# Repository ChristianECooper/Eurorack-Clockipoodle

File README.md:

### Clockipoodle
Clockipoodle is a clock module designed for use in a Eurorack modular synthesizer.

It's based on an Arduino nano, driving a Darlington Array, the UI is:
- a 128x64 pixel SSD1306 display,
- a switched rotary encoder,
- 2 x momentary buttons
- 6 x 3.5mm standard jacks

As of version 1.1 it supports the following options:
1. Direct setting of BPM via a rotary encoder.
2. Indirect setting of the BPM, using the rotary encoder to set, then pressing the encoder to apply.
3. Four additional outputs labelled A through to D that can be a multuplied, divided, duplicate or a disabled copy of the main clock.
4. Tap to set BPM.
5. Adjustable pulse width.
6. Play/Pause.
7. Reset the various outputs to be in sync again.

There is also an unused input currenly labeled as 'CV IN' and and associated LED, which may become a Clock in or CV input that drives a parameter (or parameters) to be later defined.
The current design is limited to 0-5V so could only really increase the tempo, so the next iteration is likely to support -5 to +5v so that decreasing tempo from a CV input is an option.
In the meantime I'm considering using the CV input to adjust a swing component of the beat.

All input and output jacks are protected against over voltage and negative voltages for safety.

This is my first stab at a module design, comments are welcome.

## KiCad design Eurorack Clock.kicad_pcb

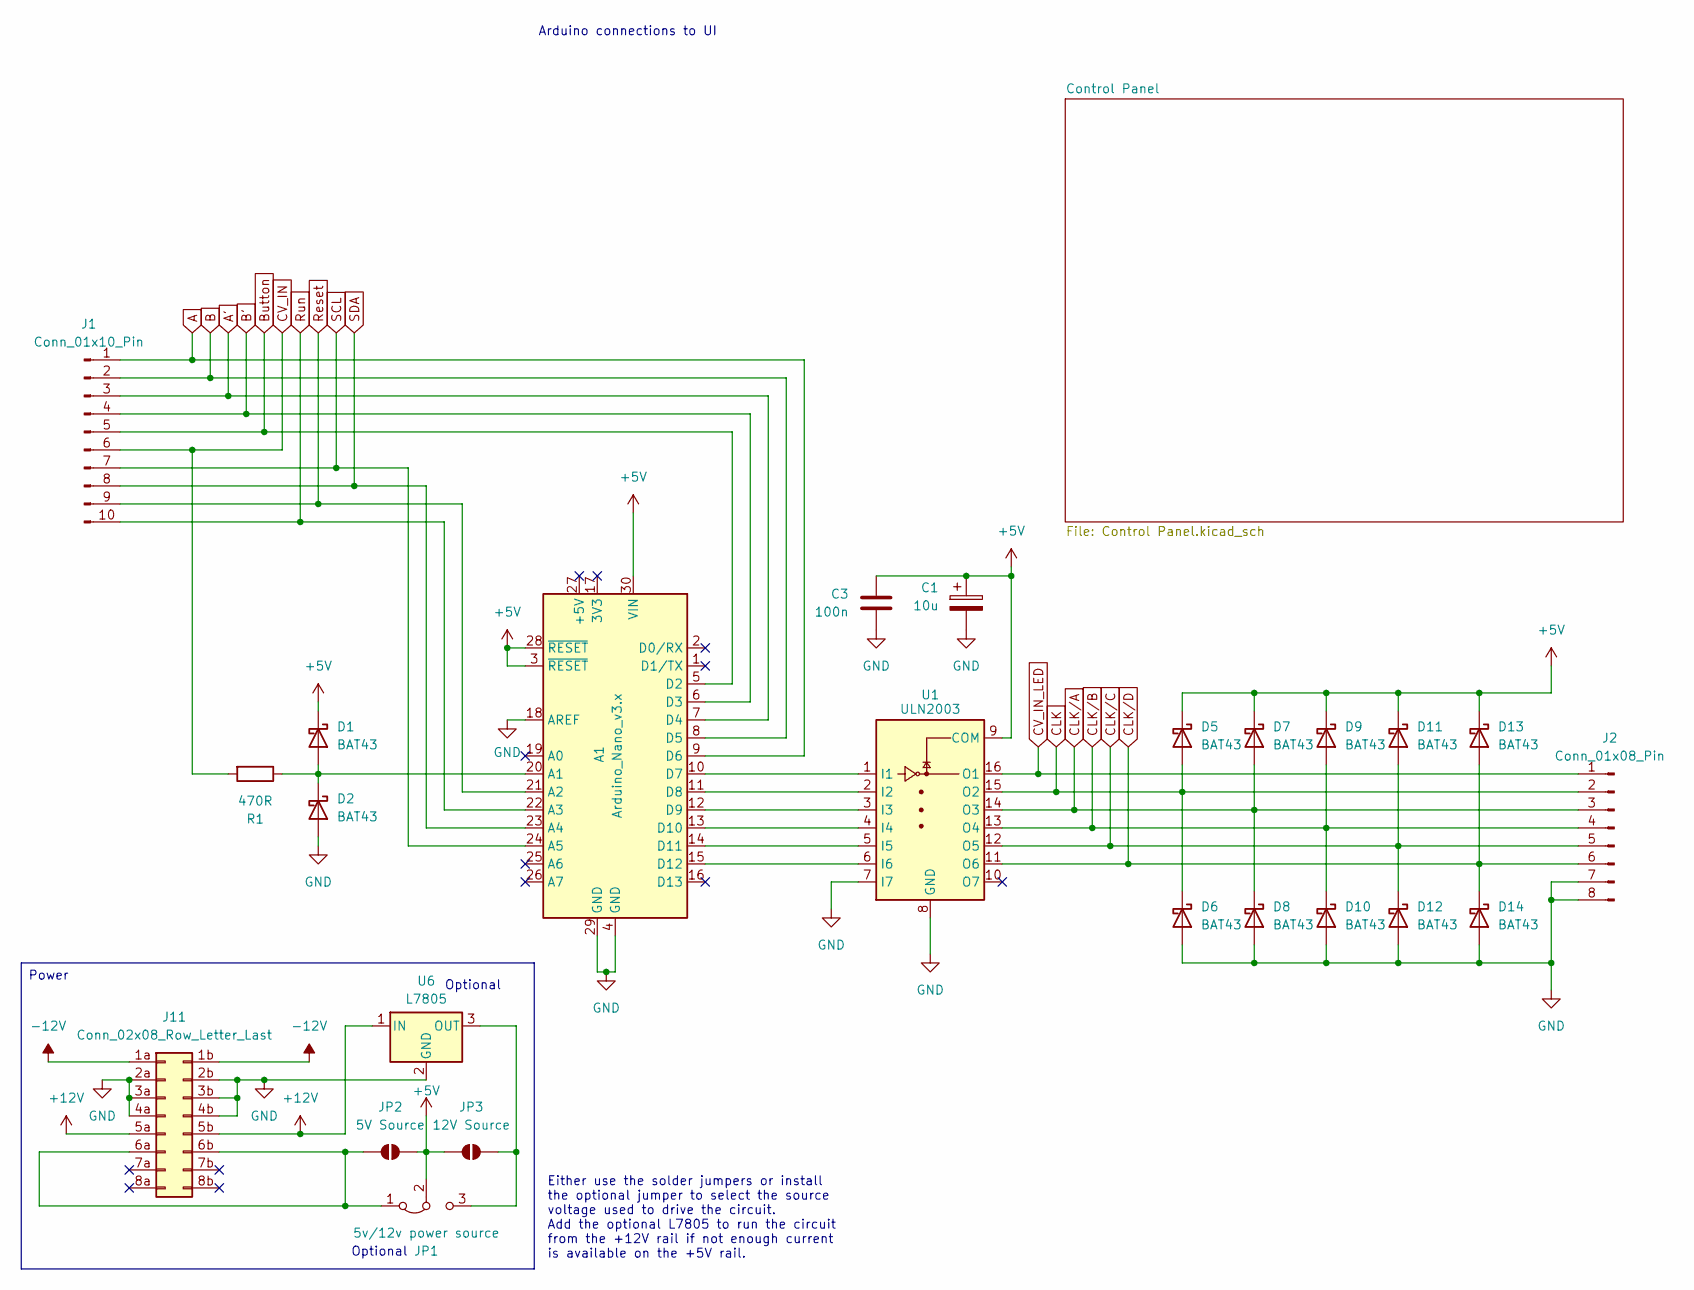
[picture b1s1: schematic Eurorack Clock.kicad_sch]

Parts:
A1: Arduino_Nano_v3.x; Arduino_Nano
C1: 10u; CP_Radial_D5.0mm_P2.50mm
C3: 100n; C_Disc_D4.7mm_W2.5mm_P5.00mm
D1, D2, D5, D6, D7, D8, D9, D10, D11, D12, D13, D14: BAT43; D_DO-35_SOD27_P2.54mm_Vertical_KathodeUp
J1: Conn_01x10_Pin; PinHeader_1x10_P2.54mm_Vertical
J2: Conn_01x08_Pin; PinHeader_1x08_P2.54mm_Vertical
J11: Conn_02x08_Row_Letter_Last; IDC-Header_2x08_P2.54mm_Vertical_Eurorack
JP1: 5v/12v power source; PinHeader_1x03_P2.54mm_Vertical
JP2: 5V Source; SolderJumper-2_P1.3mm_Open_Pad1.0x1.5mm
JP3: 12V Source; SolderJumper-2_P1.3mm_Open_Pad1.0x1.5mm
R1: 470R; R_Axial_DIN0204_L3.6mm_D1.6mm_P2.54mm_Vertical
U1: ULN2003; DIP-16_W7.62mm_Socket
U6: L7805; TO-220-3_Vertical

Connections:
+5V: A1.3 (~RESET), A1.28 (~RESET), A1.30 (VIN), C1.1, C3.1, D1.1 (K), D5.1 (K), D7.1 (K), D9.1 (K), D11.1 (K), D13.1 (K), JP1.2 (C), JP2.2 (B), JP3.1 (A), U1.9 (COM); also elsewhere on the board
+12V: J11.5a, J11.5b, U6.1 (IN)
-12V: J11.1a, J11.1b
A: A1.9 (D6), J1.1; also elsewhere on the board
A': A1.7 (D4), J1.3; also elsewhere on the board
B: A1.8 (D5), J1.2; also elsewhere on the board
B': A1.6 (D3), J1.4; also elsewhere on the board
Button: A1.5 (D2), J1.5; also elsewhere on the board
CLK: D5.2 (A), D6.1 (K), J2.2, U1.15 (O2); also elsewhere on the board
CLK/A: D7.2 (A), D8.1 (K), J2.3, U1.14 (O3); also elsewhere on the board
CLK/B: D9.2 (A), D10.1 (K), J2.4, U1.13 (O4); also elsewhere on the board
CLK/C: D11.2 (A), D12.1 (K), J2.5, U1.12 (O5); also elsewhere on the board
CLK/D: D13.2 (A), D14.1 (K), J2.6, U1.11 (O6); also elsewhere on the board
CV_IN: J1.6, R1.2; also elsewhere on the board
CV_IN_LED: J2.1, U1.16 (O1); also elsewhere on the board
GND: A1.4 (GND), A1.18 (AREF), A1.29 (GND), C1.2, C3.2, D2.2 (A), D6.2 (A), D8.2 (A), D10.2 (A), D12.2 (A), D14.2 (A), J2.7, J2.8, J11.2a, J11.2b, J11.3a, J11.3b, J11.4a, J11.4b, U1.7 (I7), U1.8 (GND), U6.2 (GND); also elsewhere on the board
unnamed: A1.20 (A1), D1.2 (A), D2.1 (K), R1.1
unnamed: A1.10 (D7), U1.1 (I1)
unnamed: A1.11 (D8), U1.2 (I2)
unnamed: A1.12 (D9), U1.3 (I3)
unnamed: A1.13 (D10), U1.4 (I4)
unnamed: A1.14 (D11), U1.5 (I5)
unnamed: A1.15 (D12), U1.6 (I6)
unnamed: J11.6a, J11.6b, JP1.1 (A), JP2.1 (A)
unnamed: JP1.3 (B), JP3.2 (B), U6.3 (OUT)
Reset: A1.21 (A2), J1.9; also elsewhere on the board
Run: A1.22 (A3), J1.10; also elsewhere on the board
SCL: A1.24 (A5), J1.7; also elsewhere on the board
SDA: A1.23 (A4), J1.8; also elsewhere on the board

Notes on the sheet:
Either use the solder jumpers or install the optional jumper to select the source voltage used to drive the circuit. Add the optional L7805 to run the circuit from the +12V rail if not enough current is available on the +5V rail.
Optional
Arduino connections to UI
Power

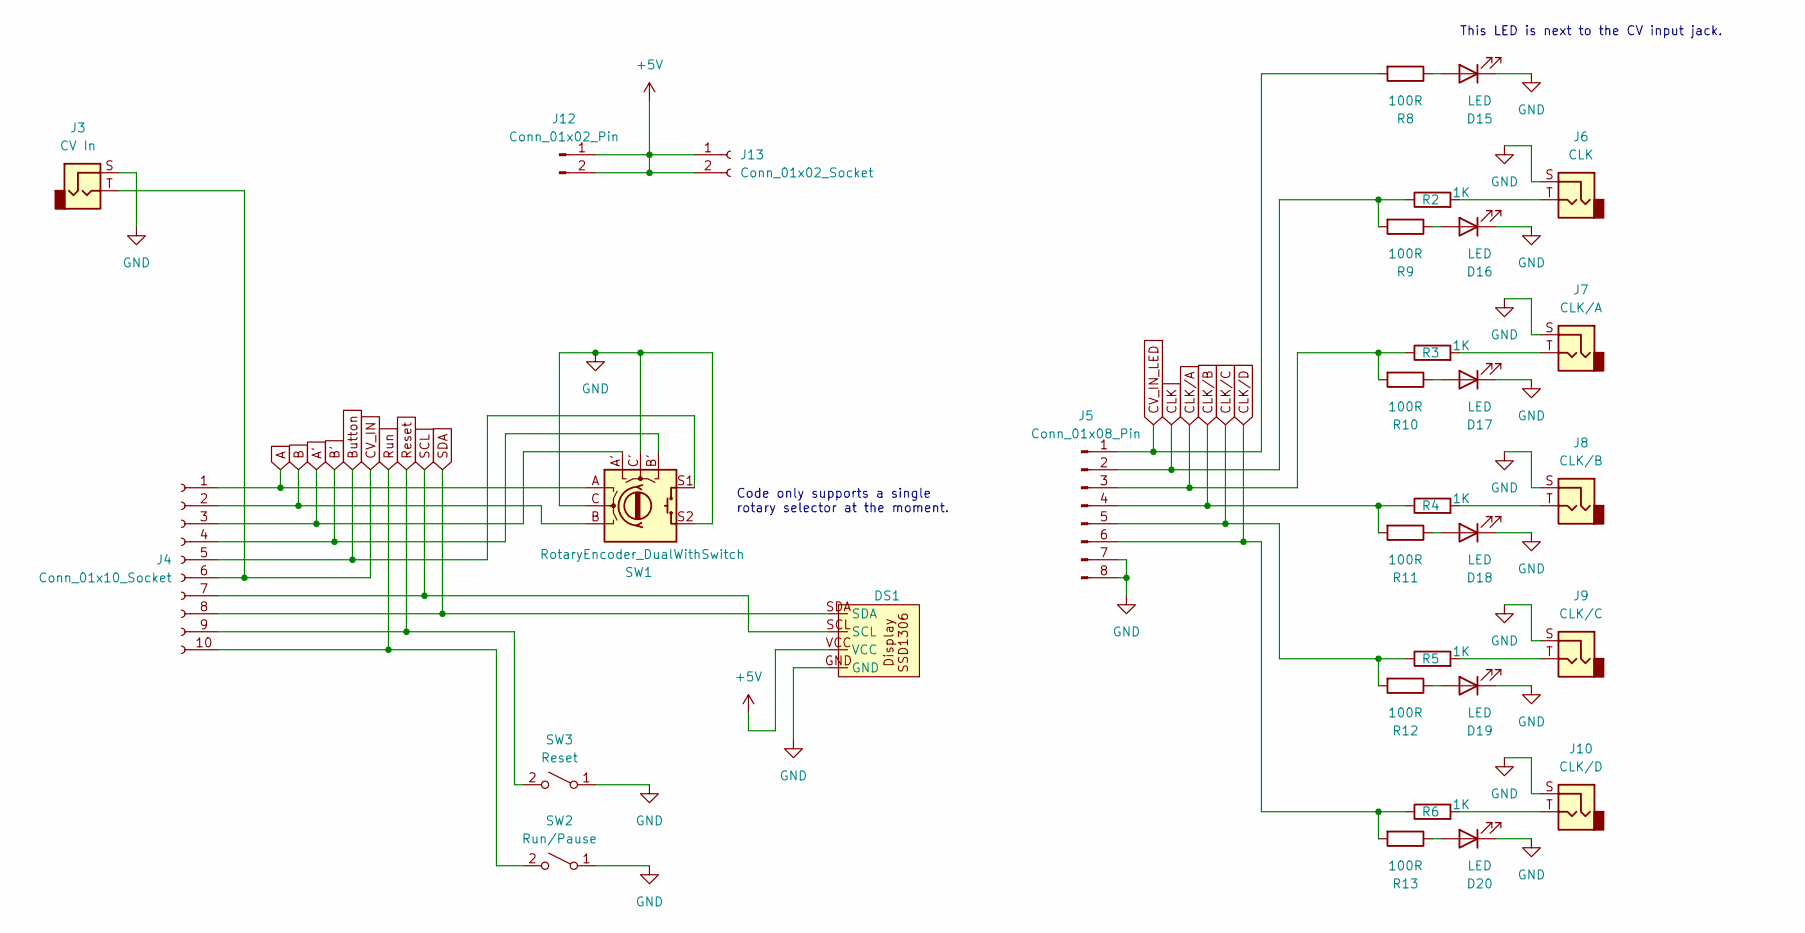
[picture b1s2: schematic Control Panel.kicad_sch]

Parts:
D15, D16, D17, D18, D19, D20: LED; LED_D3.0mm_FlatTop
DS1: SSD1306_0.96_I2C_Display
J3: CV In; Jack_3.5mm_QingPu_WQP-PJ398SM_Vertical_CircularHoles
J4: Conn_01x10_Socket; PinSocket_1x10_P2.54mm_Vertical
J5: Conn_01x08_Pin; PinSocket_1x08_P2.54mm_Vertical
J6: CLK; Jack_3.5mm_QingPu_WQP-PJ398SM_Vertical_CircularHoles
J7: CLK/A; Jack_3.5mm_QingPu_WQP-PJ398SM_Vertical_CircularHoles
J8: CLK/B; Jack_3.5mm_QingPu_WQP-PJ398SM_Vertical_CircularHoles
J9: CLK/C; Jack_3.5mm_QingPu_WQP-PJ398SM_Vertical_CircularHoles
J10: CLK/D; Jack_3.5mm_QingPu_WQP-PJ398SM_Vertical_CircularHoles
J12: Conn_01x02_Pin; PinHeader_1x02_P2.54mm_Vertical
J13: Conn_01x02_Socket; PinSocket_1x02_P2.54mm_Vertical
R2, R3, R4, R5, R6: 1K; R_Axial_DIN0204_L3.6mm_D1.6mm_P2.54mm_Vertical
R8, R9, R10, R11, R12, R13: 100R; R_Axial_DIN0204_L3.6mm_D1.6mm_P2.54mm_Vertical
SW1: RotaryEncoder_DualWithSwitch; RotaryEncoder_Vertical_H25mm_Dual_PushButton
SW2: Run/Pause; SW_PUSH_6mm_H4.3mm
SW3: Reset; SW_PUSH_6mm_H4.3mm

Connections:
+5V: DS1.VCC, J12.1, J12.2, J13.1, J13.2; also elsewhere on the board
A: J4.1, SW1.A; also elsewhere on the board
A': J4.3, SW1.A'; also elsewhere on the board
B: J4.2, SW1.B; also elsewhere on the board
B': J4.4, SW1.B'; also elsewhere on the board
Button: J4.5, SW1.S1; also elsewhere on the board
CLK: J5.2, R2.1, R9.2; also elsewhere on the board
CLK/A: J5.3, R3.1, R10.2; also elsewhere on the board
CLK/B: J5.4, R4.1, R11.2; also elsewhere on the board
CLK/C: J5.5, R5.1, R12.2; also elsewhere on the board
CLK/D: J5.6, R6.1, R13.2; also elsewhere on the board
CV_IN: J3.T, J4.6; also elsewhere on the board
CV_IN_LED: J5.1, R8.2; also elsewhere on the board
GND: D15.1 (K), D16.1 (K), D17.1 (K), D18.1 (K), D19.1 (K), D20.1 (K), DS1.GND, J3.S, J5.7, J5.8, J6.S, J7.S, J8.S, J9.S, J10.S, SW1.C, SW1.C', SW1.S2, SW2.1 (A), SW3.1 (A); also elsewhere on the board
unnamed: D15.2 (A), R8.1
unnamed: D16.2 (A), R9.1
unnamed: D17.2 (A), R10.1
unnamed: D18.2 (A), R11.1
unnamed: D19.2 (A), R12.1
unnamed: D20.2 (A), R13.1
unnamed: J6.T, R2.2
unnamed: J7.T, R3.2
unnamed: J8.T, R4.2
unnamed: J9.T, R5.2
unnamed: J10.T, R6.2
Reset: J4.9, SW3.2 (B); also elsewhere on the board
Run: J4.10, SW2.2 (B); also elsewhere on the board
SCL: DS1.SCL, J4.7; also elsewhere on the board
SDA: DS1.SDA, J4.8; also elsewhere on the board

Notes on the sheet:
Code only supports a single rotary selector at the moment.
This LED is next to the CV input jack.

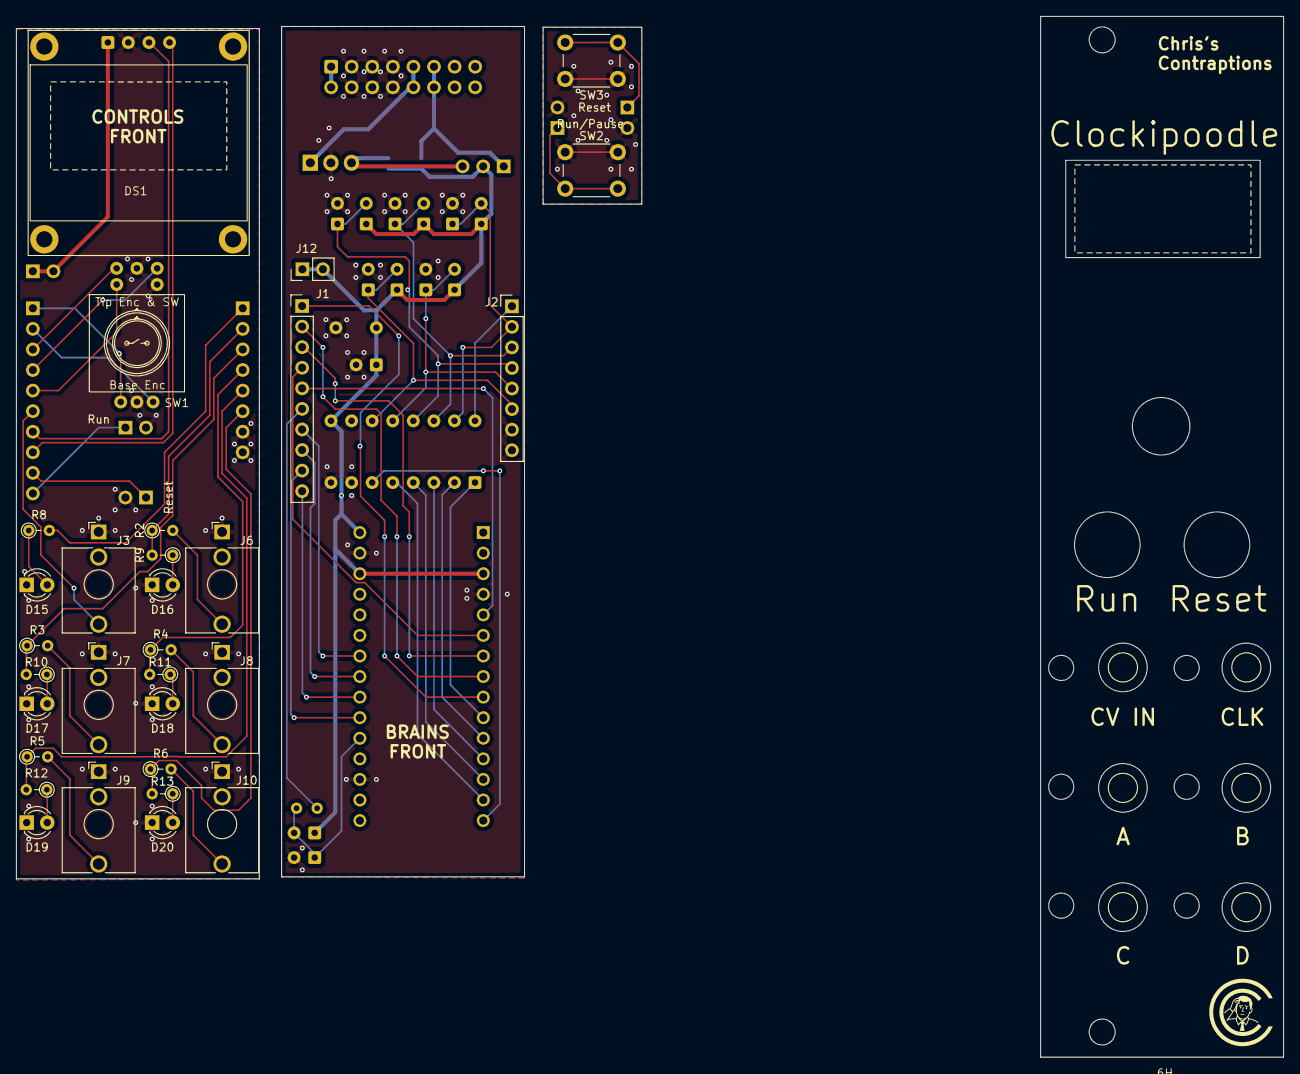
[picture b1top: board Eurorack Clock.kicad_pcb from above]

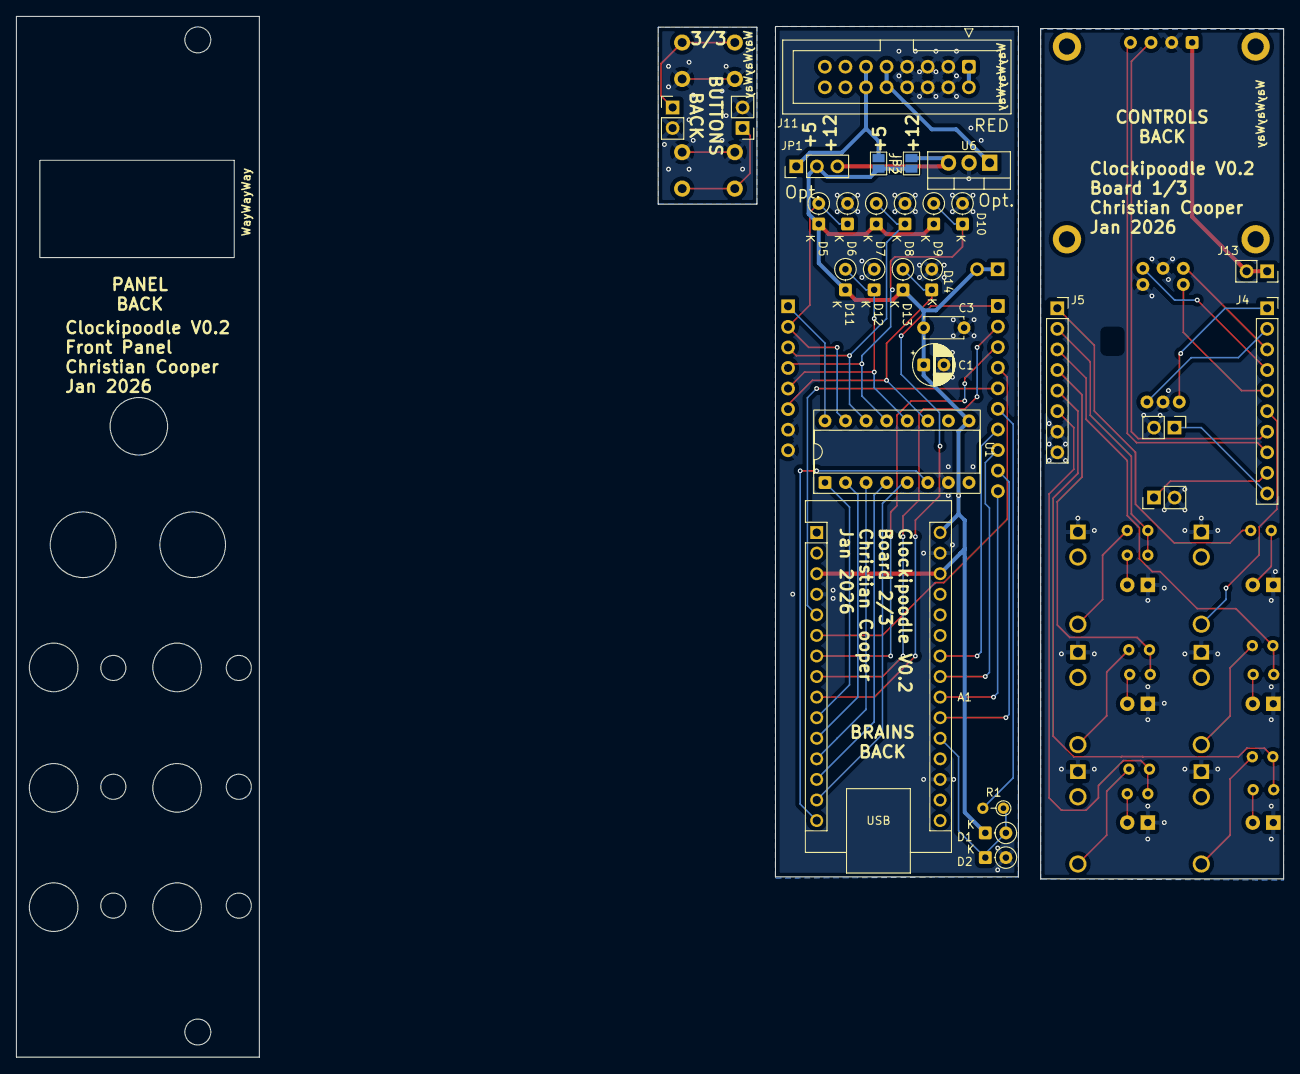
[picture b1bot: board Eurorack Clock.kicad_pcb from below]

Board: 2 copper layers, 156.5 x 128.5 mm, 77 parts (29 on the bottom side), 40 nets.

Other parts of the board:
6H: MountingHoles_6H_Panel
D15X, D16X, D17X, D18X, D19X, D20X: LED; MountingHole_3.1mm_LED_D3.0mm_FlatTop
DS1X: MoutingHole_24x12mm_SSD1306_0.96_I2C_Display
J3X: CV IN; MountingHole_6.0mm_Jack_3.5mm_QingPu_Vertical
J6X: CLK; MountingHole_6.0mm_Jack_3.5mm_QingPu_Vertical
J7X: CLK/2; MountingHole_6.0mm_Jack_3.5mm_QingPu_Vertical
J8X: CLK/4; MountingHole_6.0mm_Jack_3.5mm_QingPu_Vertical
J9X: CLK/8; MountingHole_6.0mm_Jack_3.5mm_QingPu_Vertical
J10X: CLK/16; MountingHole_6.0mm_Jack_3.5mm_QingPu_Vertical
LOGO***: LOGO; cc_logo
REF_Reset: PinHeader_1x02_P2.54mm_Vertical
REF_Run: PinHeader_1x02_P2.54mm_Vertical
Reset: PinHeader_1x02_P2.54mm_Vertical
Run: PinHeader_1x02_P2.54mm_Vertical
SW1X: RotaryEncoder_DualWithSwitch; MountingHole_7.1mm_RotaryEncoder_Vertical_H25mm_Dual_PushBu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
SW2X: Run/Stop; MountingHole_8.1mm_SW_PUSH_6x6mm
SW3X: Reset; MountingHole_8.1mm_SW_PUSH_6x6mm

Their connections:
GND: REF_Reset.2, REF_Run.2, Reset.2, Run.2; also elsewhere on the board
Reset: REF_Reset.1, Reset.1; also elsewhere on the board
Run: REF_Run.1, Run.1; also elsewhere on the board

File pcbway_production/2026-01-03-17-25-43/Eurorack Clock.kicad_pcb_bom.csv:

Designator,Quantity,Value,Footprint,Package,MPN,DNP,Mount_Type,Description,Sim.Pins
A1,1,Arduino_Nano_v3.x,Arduino_Nano,,,,tht,Arduino Nano v3.x,
C1,1,0.1u,CP_Radial_D10.0mm_P2.50mm,,,,tht,Polarized capacitor,
"D1, D10, D11, D12, D13, D14, D2, D5, D6, D7, D8, D9",12,BAT43,D_DO-35_SOD27_P2.54mm_Vertical_KathodeUp,,,,tht,"30V 0.2A Small Signal Schottky Diode, DO-35",
"D15, D16, D17, D18, D19, D20",6,LED,LED_D3.0mm_FlatTop,,,,tht,Light emitting diode,1=K 2=A
DS1,1,~,SSD1306_0.96_I2C_Display,,,,smt,,
J1,1,Conn_01x10_Pin,PinHeader_1x10_P2.54mm_Vertical,,,,tht,"Generic connector, single row, 01x10, script generated",
J10,1,CLK/16,Jack_3.5mm_QingPu_WQP-PJ398SM_Vertical_CircularHoles,,,,tht,"Audio Jack, 2 Poles (Mono / TS)",
J11,1,Conn_02x08_Row_Letter_Last,IDC-Header_2x08_P2.54mm_Vertical_Eurorack,,,,tht,"Generic connector, double row, 02x08, row letter last pin numbering scheme (pin number consists of a letter for the row and a number for the pin index in this row. 1a, ..., Na; 1b, ..., Nb)), script generated (kicad-library-utils/schlib/autogen/connector/)",
J12,1,Conn_01x02_Pin,PinHeader_1x02_P2.54mm_Vertical,,,,tht,"Generic connector, single row, 01x02, script generated",
J13,1,Conn_01x02_Socket,PinSocket_1x02_P2.54mm_Vertical,,,,tht,"Generic connector, single row, 01x02, script generated",
J2,1,Conn_01x08_Pin,PinHeader_1x08_P2.54mm_Vertical,,,,tht,"Generic connector, single row, 01x08, script generated",
J3,1,Clock In,Jack_3.5mm_QingPu_WQP-PJ398SM_Vertical_CircularHoles,,,,tht,"Audio Jack, 2 Poles (Mono / TS)",
J4,1,Conn_01x10_Socket,PinSocket_1x10_P2.54mm_Vertical,,,,tht,"Generic connector, single row, 01x10, script generated",
J5,1,Conn_01x08_Pin,PinSocket_1x08_P2.54mm_Vertical,,,,tht,"Generic connector, single row, 01x08, script generated",
J6,1,CLK,Jack_3.5mm_QingPu_WQP-PJ398SM_Vertical_CircularHoles,,,,tht,"Audio Jack, 2 Poles (Mono / TS)",
J7,1,CLK/2,Jack_3.5mm_QingPu_WQP-PJ398SM_Vertical_CircularHoles,,,,tht,"Audio Jack, 2 Poles (Mono / TS)",
J8,1,CLK/4,Jack_3.5mm_QingPu_WQP-PJ398SM_Vertical_CircularHoles,,,,tht,"Audio Jack, 2 Poles (Mono / TS)",
J9,1,CLK/8,Jack_3.5mm_QingPu_WQP-PJ398SM_Vertical_CircularHoles,,,,tht,"Audio Jack, 2 Poles (Mono / TS)",
R1,1,470R,R_Axial_DIN0204_L3.6mm_D1.6mm_P2.54mm_Vertical,,,,tht,Resistor,
"R10, R11, R12, R13, R8, R9",6,100R,R_Axial_DIN0204_L3.6mm_D1.6mm_P2.54mm_Vertical,,,,tht,Resistor,
"R2, R3, R4, R5, R6",5,1K,R_Axial_DIN0204_L3.6mm_D1.6mm_P2.54mm_Vertical,,,,tht,Resistor,
"REF_Reset, REF_Run, Reset, Run",4,PinHeader_1x02_P2.54mm_Vertical,PinHeader_1x02_P2.54mm_Vertical,,,,tht,,
"REF_Stand1, REF_Stand1A, REF_Stand2, REF_Stand2A",4,PinHeader_1x01_P2.54mm_Vertical,PinHeader_1x01_P2.54mm_Vertical,,,,tht,,
SW1,1,RotaryEncoder_DualWithSwitch,RotaryEncoder_Vertical_H25mm_Dual_PushButton,,,,smt,"Rotary encoder, dual channel, incremental quadrate outputs, with switch",
SW2,1,Run/Stop,SW_PUSH_6mm_H4.3mm,,,,tht,Single Pole Single Throw (SPST) switch,
SW3,1,Reset,SW_PUSH_6mm_H4.3mm,,,,tht,Single Pole Single Throw (SPST) switch,
U1,1,ULN2003,DIP-16_W7.62mm_Socket,,,,tht,"High Voltage, High Current Darlington Transistor Arrays, SOIC16/SOIC16W/DIP16/TSSOP16",
U6,1,L7805,TO-220-3_Vertical,,,,tht,"Positive 1.5A 35V Linear Regulator, Fixed Output 5V, TO-220/TO-263/TO-252",

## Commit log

2026-01-27 Initial KiCad commit
2026-01-27 Added Arduino code
2026-01-27 Added code comments and fixed directory structure
2026-01-27 Updated labels on front panel
2026-01-28 Relabeled outputs on schematic and panel, cleaned up pcb layout, removed unused headers, added logo - still need to add to panel
2026-01-28 Removed overflow bug and removed BPM animation
2026-01-28 Removed debugging logging
